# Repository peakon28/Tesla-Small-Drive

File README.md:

# Tesla-Small-Drive

Tesla Model S and X Small Drive unit based on Damien Maguire design using Open Inverter software by Johanes Hubner. Design in Kicad 9
<br>
(

<br>

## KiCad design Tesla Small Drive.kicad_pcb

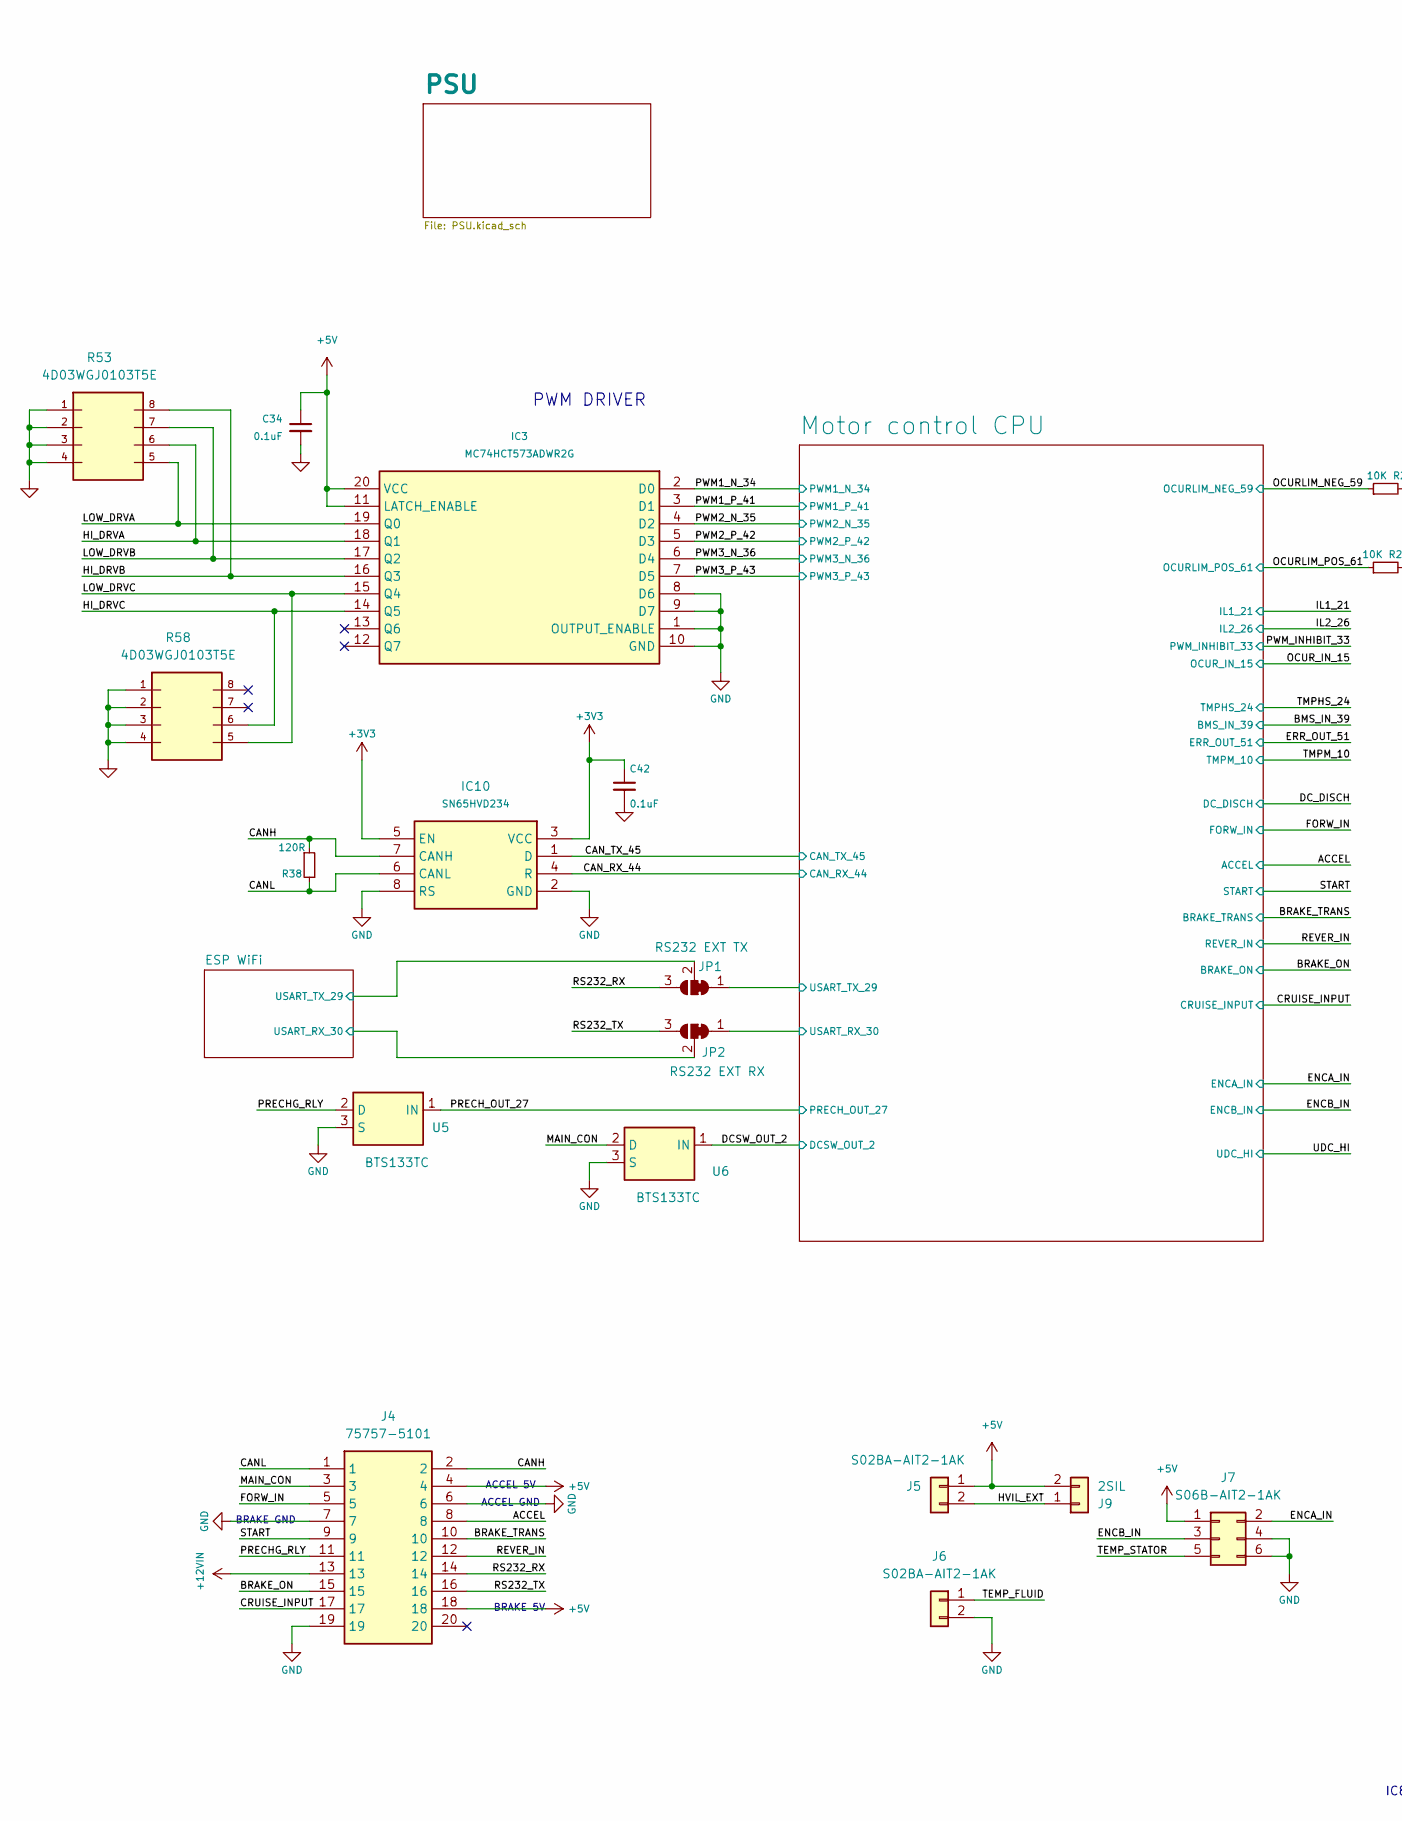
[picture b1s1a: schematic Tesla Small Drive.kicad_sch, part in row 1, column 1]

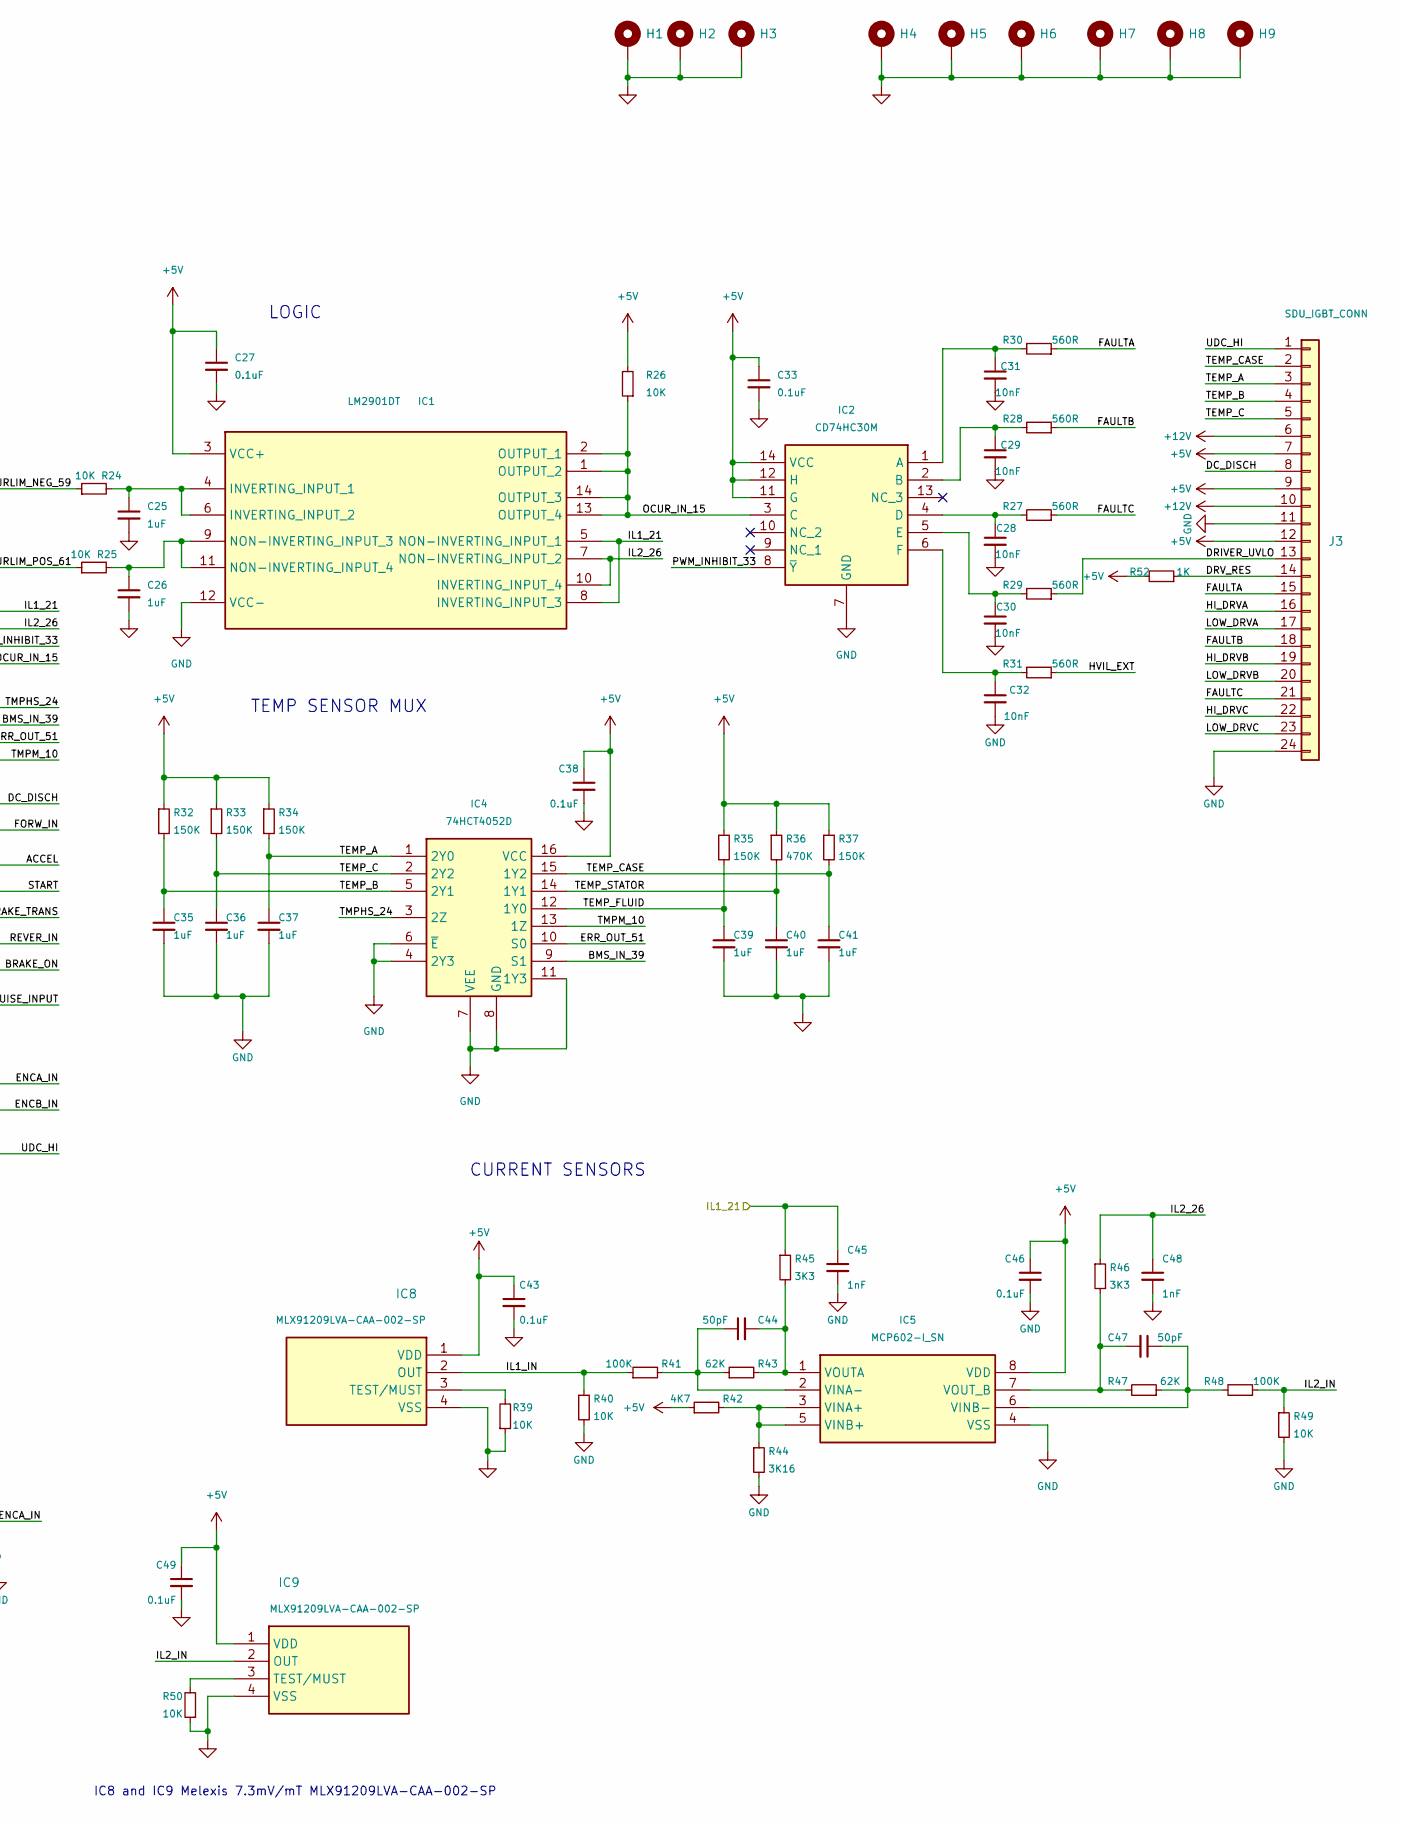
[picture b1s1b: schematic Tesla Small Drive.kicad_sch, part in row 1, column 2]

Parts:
C25, C26, C35, C36, C37, C39, C40, C41: 1uF; C_0603_1608Metric
C27, C33, C34, C38, C42, C43, C46, C49: 0.1uF; C_0603_1608Metric
C28, C29, C30, C31, C32: 10nF; C_0603_1608Metric
C44, C47: 50pF; C_0603_1608Metric
C45, C48: 1nF; C_0603_1608Metric
H1, H2, H3, H4, H5, H6, H7, H8, H9: MountingHole_Pad; MountingHole_4mm_Pad_Via
IC1: LM2901DT; SOIC127P600X175-14N; Manufacturer_Part_Number LM2901DT; Mouser Part Number 511-LM2901DT
IC2: CD74HC30M; SOIC127P600X175-14N; Manufacturer_Part_Number CD74HC30M; Mouser Part Number 595-CD74HC30M
IC3: MC74HCT573ADWR2G; SOIC-20; Manufacturer_Part_Number MC74HCT573ADWR2G; Mouser Part Number 863-MC74HCT573ADWR2G
IC4: 74HCT4052D; SOIC127P600X175-16N; Manufacturer_Part_Number 74HCT4052D; Mouser Part Number 771-74HCT4052D
IC5: MCP602-I_SN; SOIC127P600X175-8N; Manufacturer_Part_Number MCP602-I/SN; Mouser Part Number 579-MCP602ISN
IC8, IC9: MLX91209LVA-CAA-002-SP; MLX91209LVACAA002SP; Manufacturer_Part_Number MLX91209LVA-CAA-002-SP; Mouser Part Number 482-91209LVACAA002SP
IC10: SN65HVD234; SOIC127P599X175-8N; Manufacturer_Part_Number SN65HVD234DR; Mouser Part Number 595-SN65HVD234DR
J3: SDU_IGBT_CONN; RHDR24W76P254_2X12_3048X508X826P
J4: 75757-5101; 75757-5101 footprint; Manufacturer_Part_Number 75757-5101; Mouser Part Number 538-75757-5101
J5, J6: S02BA-AIT2-1AK
J7: S06B-AIT2-1AK
J9: 2SIL; PinHeader_1x02_P2.54mm_Vertical
JP1: RS232 EXT TX; SolderJumper-3_P1.3mm_Bridged12_RoundedPad1.0x1.5mm
JP2: RS232 EXT RX; SolderJumper-3_P1.3mm_Bridged12_RoundedPad1.0x1.5mm
R24, R25, R26, R39, R40, R49, R50: 10K; R_0603_1608Metric
R27, R28, R29, R30, R31: 560R; R_0603_1608Metric
R32, R33, R34, R35, R37: 150K; R_0603_1608Metric
R36: 470K; R_0603_1608Metric
R38: 120R; R_0603_1608Metric
R41, R48: 100K; R_0603_1608Metric
R42: 4K7; R_0603_1608Metric
R43, R47: 62K; R_0603_1608Metric
R44: 3K16; R_0603_1608Metric
R45, R46: 3K3; R_0603_1608Metric
R52: 1K; R_0603_1608Metric
R53, R58: 4D03WGJ0103T5E; RESCAXS80P320X160X60-8N; PARTREV N/A
U5, U6: BTS133TC; TO254P1524X457-3N

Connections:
+3V3: C42.1, IC10.3 (VCC), IC10.5 (EN); also elsewhere on the board
+5V: C27.1, C33.1, C34.1, C38.1, C43.1, C46.1, C49.1, IC1.3 (VCC+), IC2.11 (G), IC2.12 (H), IC2.14 (VCC), IC3.11 (LATCH_ENABLE), IC3.20 (VCC), IC4.16 (VCC), IC5.8 (VDD), IC8.1 (VDD), IC9.1 (VDD), J3.7, J3.9, J3.12, J4.4, J4.18, J5.1, J7.1, J9.2, R26.2, R32.1, R33.1, R34.1, R35.1, R36.1, R37.1, R42.1, R52.2; also elsewhere on the board
+12V: J3.6, J3.10; also elsewhere on the board
+12VIN: J4.13; also elsewhere on the board
/ACCEL: J4.8; also elsewhere on the board
/BMS_IN_39: IC4.9 (S1); also elsewhere on the board
/BRAKE_ON: J4.15; also elsewhere on the board
/BRAKE_TRANS: J4.10; also elsewhere on the board
/CANH: IC10.7 (CANH), J4.2, R38.1
/CANL: IC10.6 (CANL), J4.1, R38.2
/CAN_RX_44: IC10.4 (R); also elsewhere on the board
/CAN_TX_45: IC10.1 (D); also elsewhere on the board
/CRUISE_INPUT: J4.17; also elsewhere on the board
/DCSW_OUT_2: U6.1 (IN); also elsewhere on the board
/DC_DISCH: J3.8; also elsewhere on the board
/DRIVER_UVLO: J3.13, R29.1
/DRV_RES: J3.14, R52.1
/ENCA_IN: J7.2; also elsewhere on the board
/ENCB_IN: J7.3; also elsewhere on the board
/ERR_OUT_51: IC4.10 (S0); also elsewhere on the board
/ESP WiFi/RX: JP1.2 (C); also elsewhere on the board
/ESP WiFi/TX: JP2.2 (C); also elsewhere on the board
/FAULTA: J3.15, R30.1
/FAULTB: J3.18, R28.1
/FAULTC: J3.21, R27.1
/FORW_IN: J4.5; also elsewhere on the board
/HI_DRVA: IC3.18 (Q1), J3.16, R53.6
/HI_DRVB: IC3.16 (Q3), J3.19, R53.8
/HI_DRVC: IC3.14 (Q5), J3.22, R58.6
/HVIL_EXT: J5.2, J9.1, R31.1
/IL1_21: C45.1, IC1.5 (NON-INVERTING_INPUT_1), IC1.8 (INVERTING_INPUT_3), R45.1; also elsewhere on the board
/IL1_IN: IC8.2 (OUT), R40.1, R41.1
/IL2_26: C48.1, IC1.7 (NON-INVERTING_INPUT_2), IC1.10 (INVERTING_INPUT_4), R46.1; also elsewhere on the board
/IL2_IN: IC9.2 (OUT), R48.1, R49.1
/LOW_DRVA: IC3.19 (Q0), J3.17, R53.5
/LOW_DRVB: IC3.17 (Q2), J3.20, R53.7
/LOW_DRVC: IC3.15 (Q4), J3.23, R58.5
/MAIN_CON: J4.3, U6.2 (D)
/Motor control CPU/USART_RX_30: JP2.1 (A); also elsewhere on the board
/Motor control CPU/USART_TX_29: JP1.1 (A); also elsewhere on the board
/OCURLIM_NEG_59: R24.1; also elsewhere on the board
/OCURLIM_POS_61: R25.1; also elsewhere on the board
/OCUR_IN_15: IC1.1 (OUTPUT_2), IC1.2 (OUTPUT_1), IC1.13 (OUTPUT_4), IC1.14 (OUTPUT_3), IC2.3 (C), R26.1; also elsewhere on the board
/PRECHG_RLY: J4.11, U5.2 (D)
/PRECH_OUT_27: U5.1 (IN); also elsewhere on the board
/PWM1_N_34: IC3.2 (D0); also elsewhere on the board
/PWM1_P_41: IC3.3 (D1); also elsewhere on the board
/PWM2_N_35: IC3.4 (D2); also elsewhere on the board
/PWM2_P_42: IC3.5 (D3); also elsewhere on the board
/PWM3_N_36: IC3.6 (D4); also elsewhere on the board
/PWM3_P_43: IC3.7 (D5); also elsewhere on the board
/PWM_INHIBIT_33: IC2.8 (~Y); also elsewhere on the board
/REVER_IN: J4.12; also elsewhere on the board
/RS232_RX: J4.14, JP1.3 (B)
/RS232_TX: J4.16, JP2.3 (B)
/START: J4.9; also elsewhere on the board
/TEMP_A: C37.1, IC4.1 (2Y0), J3.3, R34.2
/TEMP_B: C35.1, IC4.5 (2Y1), J3.4, R32.2
/TEMP_C: C36.1, IC4.2 (2Y2), J3.5, R33.2
/TEMP_CASE: C41.1, IC4.15 (1Y2), J3.2, R37.2
/TEMP_FLUID: C39.1, IC4.12 (1Y0), J6.1, R35.2
/TEMP_STATOR: C40.1, IC4.14 (1Y1), J7.5, R36.2
/TMPHS_24: IC4.3 (2Z); also elsewhere on the board
/TMPM_10: IC4.13 (1Z); also elsewhere on the board
/UDC_HI: J3.1; also elsewhere on the board
GND: C25.2, C26.2, C27.2, C28.2, C29.2, C30.2, C31.2, C32.2, C33.2, C34.2, C35.2, C36.2, C37.2, C38.2, C39.2, C40.2, C41.2, C42.2, C43.2, C45.2, C46.2, C48.2, C49.2, H1.1, H2.1, H3.1, H4.1, H5.1, H6.1, H7.1, H8.1, H9.1, IC1.12 (VCC-), IC2.7 (GND), IC3.1 (OUTPUT_ENABLE), IC3.8 (D6), IC3.9 (D7), IC3.10 (GND), IC4.4 (2Y3), IC4.6 (~E), IC4.7 (VEE), IC4.8 (GND), IC4.11 (1Y3), IC5.4 (VSS), IC8.4 (VSS), IC9.4 (VSS), IC10.2 (GND), IC10.8 (RS), J3.11, J3.24, J4.6, J4.7, J4.19, J6.2, J7.4, J7.6, R39.1, R40.2, R44.2, R49.2, R50.1, R53.1, R53.2, R53.3, R53.4, R58.1, R58.2, R58.3, R58.4, U5.3 (S), U6.3 (S); also elsewhere on the board
unnamed: C25.1, IC1.4 (INVERTING_INPUT_1), IC1.6 (INVERTING_INPUT_2), R24.2
unnamed: C26.1, IC1.9 (NON-INVERTING_INPUT_3), IC1.11 (NON-INVERTING_INPUT_4), R25.2
unnamed: C31.1, IC2.1 (A), R30.2
unnamed: C29.1, IC2.2 (B), R28.2
unnamed: C28.1, IC2.4 (D), R27.2
unnamed: C30.1, IC2.5 (E), R29.2
unnamed: C32.1, IC2.6 (F), R31.2
unnamed: IC5.3 (VINA+), IC5.5 (VINB+), R42.2, R44.1
unnamed: C44.1, IC5.2 (VINA-), R41.2, R43.1
unnamed: C47.1, IC5.6 (VINB-), R47.1, R48.2
unnamed: C44.2, IC5.1 (VOUTA), R43.2, R45.2
unnamed: C47.2, IC5.7 (VOUT_B), R46.2, R47.2
unnamed: IC8.3 (TEST/MUST), R39.2
unnamed: IC9.3 (TEST/MUST), R50.2

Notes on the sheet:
BRAKE 5V
PWM DRIVER
IC8 and IC9 Melexis 7.3mV/mT MLX91209LVA-CAA-002-SP
TEMP SENSOR MUX
LOGIC
BRAKE GND
ACCEL GND
ACCEL 5V
CURRENT SENSORS

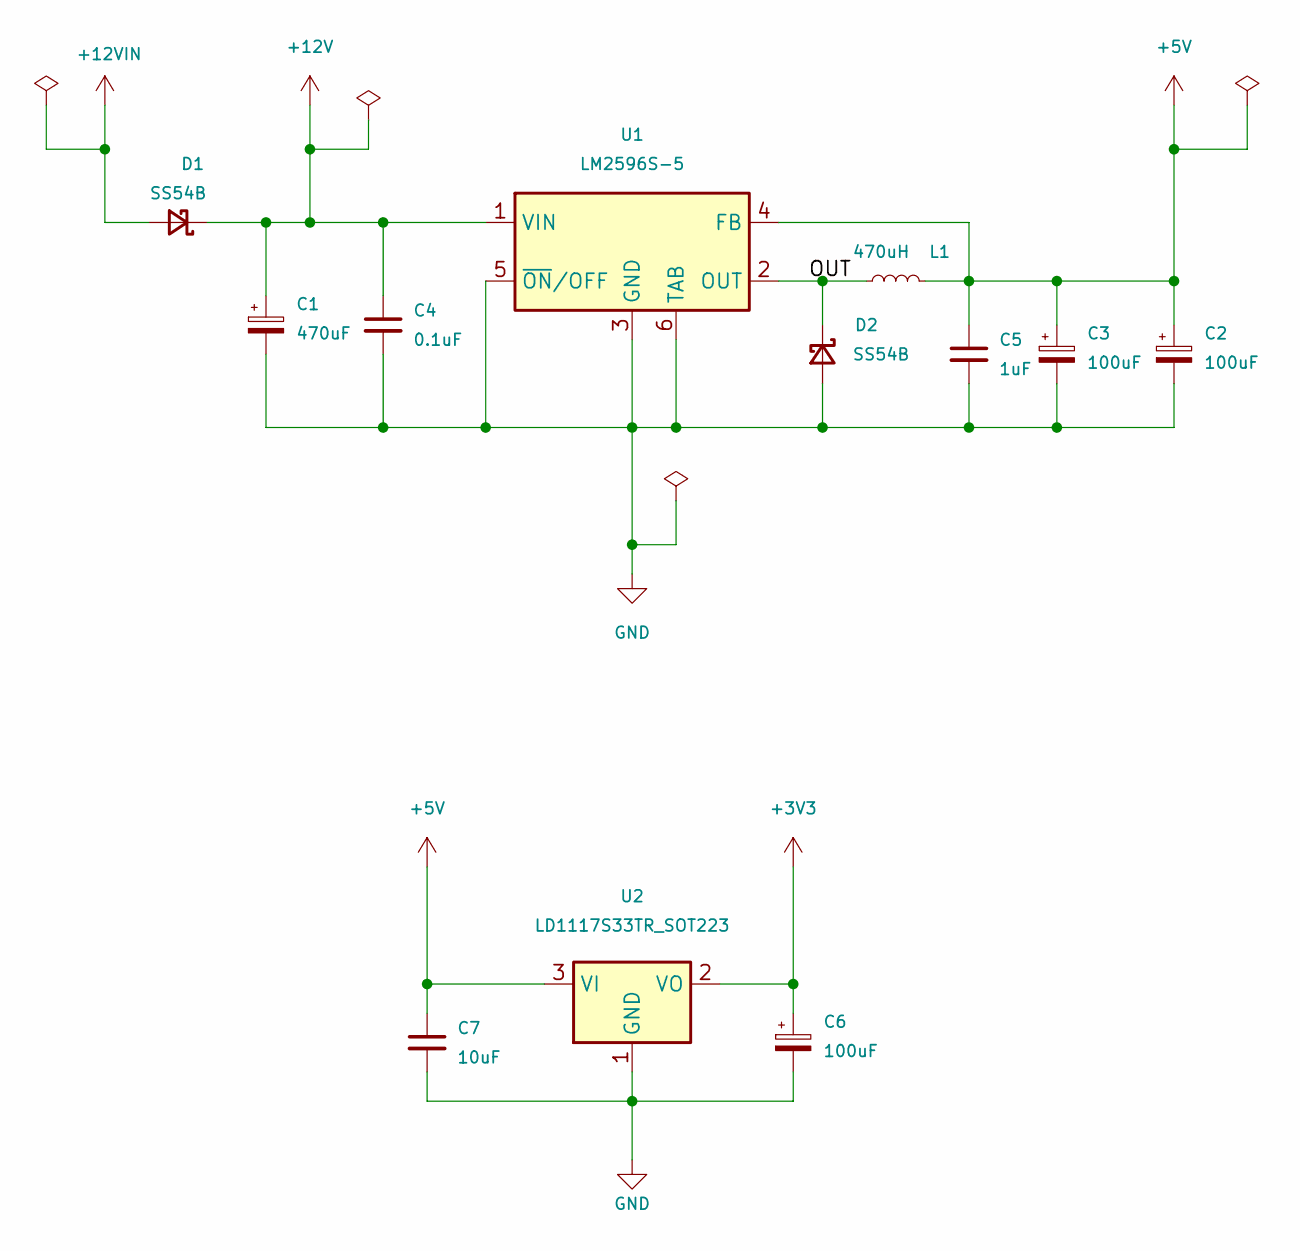
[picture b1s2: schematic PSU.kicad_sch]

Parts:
C1: 470uF; CP_Elec_10x10; JLCPCB Part # C3351
C2, C3, C6: 100uF; CP_EIA-3528-21_Kemet-B; JLCPCB Part # C16133
C4: 0.1uF; C_0603_1608Metric
C5: 1uF; C_0603_1608Metric
C7: 10uF; C_0603_1608Metric
D1, D2: SS54B; DIOM4336X244N; JLCPCB Part # C698840
L1: 470uH; L_Sunlord_SWRB1207S; JLCPCB Part # C169382
U1: LM2596S-5; TO-263-5_TabPin6; LCSC Part # C10002
U2: LD1117S33TR_SOT223; SOT-223-3_TabPin2; JLCPCB Part # C347229

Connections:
+3V3: C6.1, U2.2 (VO); also elsewhere on the board
+5V: C2.1, C3.1, C5.1, C7.1, L1.2, U1.4 (FB), U2.3 (VI); also elsewhere on the board
+12V: C1.1, C4.1, D1.C (K), U1.1 (VIN); also elsewhere on the board
+12VIN: D1.A; also elsewhere on the board
/PSU/OUT: D2.C (K), L1.1, U1.2 (OUT)
GND: C1.2, C2.2, C3.2, C4.2, C5.2, C6.2, C7.2, D2.A, U1.3 (GND), U1.5 (~ON/OFF), U1.6 (TAB), U2.1 (GND); also elsewhere on the board

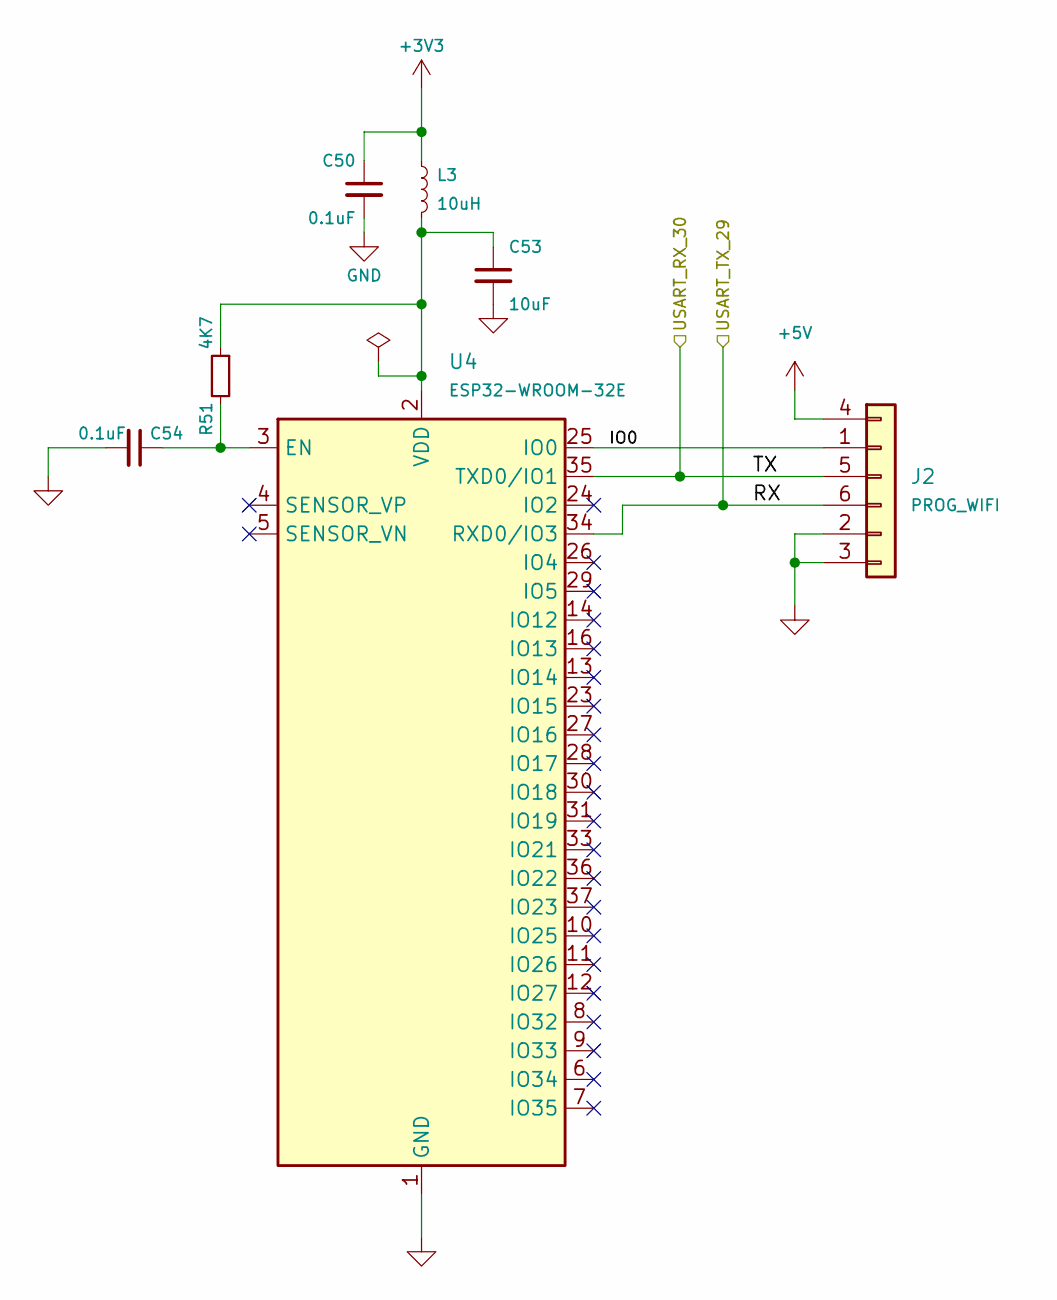
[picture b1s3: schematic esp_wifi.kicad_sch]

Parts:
C50, C54: 0.1uF; C_0603_1608Metric
C53: 10uF; C_0603_1608Metric
J2: PROG_WIFI; PinHeader_1x06_P2.54mm_Vertical
L3: 10uH; L_0603_1608Metric
R51: 4K7; R_0603_1608Metric
U4: ESP32-WROOM-32E; ESP32-WROOM-32D

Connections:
+3V3: C50.1, L3.1; also elsewhere on the board
+5V: J2.4; also elsewhere on the board
/ESP WiFi/IO0: J2.1, U4.25 (IO0)
/ESP WiFi/RX: J2.6, U4.34 (RXD0/IO3); also elsewhere on the board
/ESP WiFi/TX: J2.5, U4.35 (TXD0/IO1); also elsewhere on the board
GND: C50.2, C53.2, C54.2, J2.2, J2.3, U4.1 (GND), U4.15 (GND), U4.38 (GND), U4.39 (GND); also elsewhere on the board
unnamed: C54.1, R51.2, U4.3 (EN)
unnamed: C53.1, L3.2, R51.1, U4.2 (VDD)

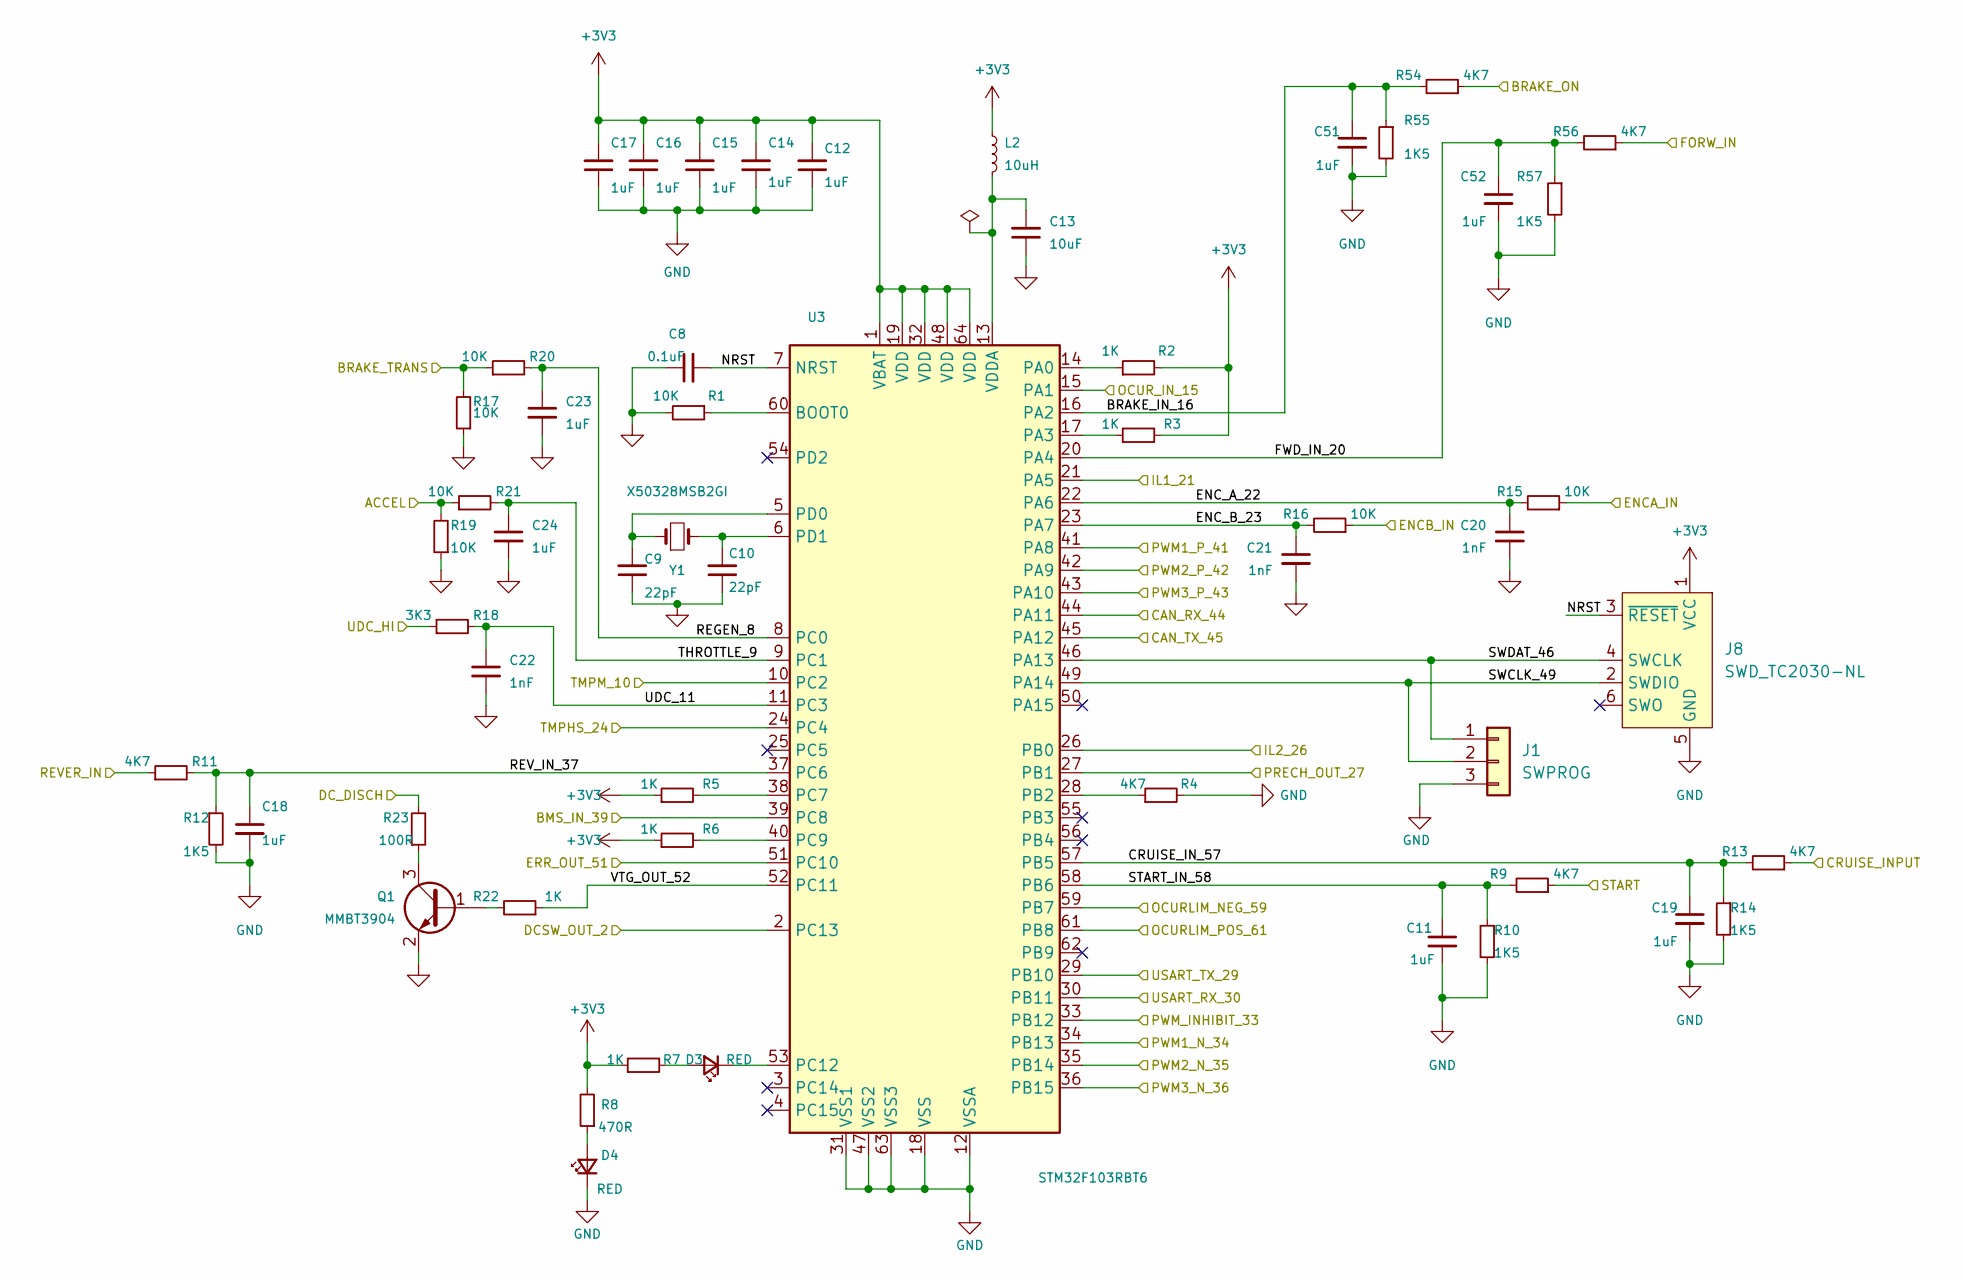
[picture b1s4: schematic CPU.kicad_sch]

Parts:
C8: 0.1uF; C_0603_1608Metric
C9, C10: 22pF; C_0603_1608Metric
C11, C12, C14, C15, C16, C17, C18, C19, C23, C24, C51, C52: 1uF; C_0603_1608Metric
C13: 10uF; C_0603_1608Metric
C20, C21, C22: 1nF; C_0603_1608Metric
D3, D4: RED; LED_0603_1608Metric
J1: SWPROG; PinHeader_1x03_P2.54mm_Vertical
J8: SWD_TC2030-NL; Tag-Connect_TC2030-IDC-NL_2x03_P1.27mm_Vertical
L2: 10uH; L_0603_1608Metric
Q1: MMBT3904; SOT-23
R1, R15, R16, R17, R19, R20, R21: 10K; R_0603_1608Metric
R2, R3, R5, R6, R7, R22: 1K; R_0603_1608Metric
R4, R9, R11, R13, R54, R56: 4K7; R_0603_1608Metric
R8: 470R; R_0603_1608Metric
R10, R12, R14, R55, R57: 1K5; R_0603_1608Metric
R18: 3K3; R_0603_1608Metric
R23: 100R; R_0603_1608Metric
U3: STM32F103RBT6; LQFP-64_10x10mm_P0.5mm
Y1: X50328MSB2GI; RESC5032X135N

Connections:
+3V3: C12.2, C14.2, C15.2, C16.2, C17.2, J8.1 (VCC), L2.1, R2.2, R3.2, R5.1, R6.1, R7.1, R8.2, U3.1 (VBAT), U3.19 (VDD), U3.32 (VDD), U3.48 (VDD), U3.64 (VDD); also elsewhere on the board
/ACCEL: R19.2, R21.1; also elsewhere on the board
/BMS_IN_39: U3.39 (PC8); also elsewhere on the board
/BRAKE_ON: R54.1; also elsewhere on the board
/BRAKE_TRANS: R17.2, R20.1; also elsewhere on the board
/CAN_RX_44: U3.44 (PA11); also elsewhere on the board
/CAN_TX_45: U3.45 (PA12); also elsewhere on the board
/CRUISE_INPUT: R13.1; also elsewhere on the board
/DCSW_OUT_2: U3.2 (PC13); also elsewhere on the board
/DC_DISCH: R23.2; also elsewhere on the board
/ENCA_IN: R15.1; also elsewhere on the board
/ENCB_IN: R16.1; also elsewhere on the board
/ERR_OUT_51: U3.51 (PC10); also elsewhere on the board
/FORW_IN: R56.1; also elsewhere on the board
/IL1_21: U3.21 (PA5); also elsewhere on the board
/IL2_26: U3.26 (PB0); also elsewhere on the board
/Motor control CPU/BRAKE_IN_16: C51.1, R54.2, R55.1, U3.16 (PA2)
/Motor control CPU/CRUISE_IN_57: C19.1, R13.2, R14.1, U3.57 (PB5)
/Motor control CPU/ENC_A_22: C20.1, R15.2, U3.22 (PA6)
/Motor control CPU/ENC_B_23: C21.1, R16.2, U3.23 (PA7)
/Motor control CPU/FWD_IN_20: C52.1, R56.2, R57.1, U3.20 (PA4)
/Motor control CPU/NRST: C8.2, J8.3 (~RESET), U3.7 (NRST)
/Motor control CPU/REGEN_8: C23.1, R20.2, U3.8 (PC0)
/Motor control CPU/REV_IN_37: C18.1, R11.2, R12.1, U3.37 (PC6)
/Motor control CPU/START_IN_58: C11.1, R9.2, R10.1, U3.58 (PB6)
/Motor control CPU/SWCLK_49: J1.2, J8.2 (SWDIO), U3.49 (PA14)
/Motor control CPU/SWDAT_46: J1.1, J8.4 (SWCLK), U3.46 (PA13)
/Motor control CPU/THROTTLE_9: C24.1, R21.2, U3.9 (PC1)
/Motor control CPU/UDC_11: C22.1, R18.2, U3.11 (PC3)
/Motor control CPU/USART_RX_30: U3.30 (PB11); also elsewhere on the board
/Motor control CPU/USART_TX_29: U3.29 (PB10); also elsewhere on the board
/Motor control CPU/VTG_OUT_52: R22.1, U3.52 (PC11)
/OCURLIM_NEG_59: U3.59 (PB7); also elsewhere on the board
/OCURLIM_POS_61: U3.61 (PB8); also elsewhere on the board
/OCUR_IN_15: U3.15 (PA1); also elsewhere on the board
/PRECH_OUT_27: U3.27 (PB1); also elsewhere on the board
/PWM1_N_34: U3.34 (PB13); also elsewhere on the board
/PWM1_P_41: U3.41 (PA8); also elsewhere on the board
/PWM2_N_35: U3.35 (PB14); also elsewhere on the board
/PWM2_P_42: U3.42 (PA9); also elsewhere on the board
/PWM3_N_36: U3.36 (PB15); also elsewhere on the board
/PWM3_P_43: U3.43 (PA10); also elsewhere on the board
/PWM_INHIBIT_33: U3.33 (PB12); also elsewhere on the board
/REVER_IN: R11.1; also elsewhere on the board
/START: R9.1; also elsewhere on the board
/TMPHS_24: U3.24 (PC4); also elsewhere on the board
/TMPM_10: U3.10 (PC2); also elsewhere on the board
/UDC_HI: R18.1; also elsewhere on the board
GND: C8.1, C9.1, C10.1, C11.2, C12.1, C13.1, C14.1, C15.1, C16.1, C17.1, C18.2, C19.2, C20.2, C21.2, C22.2, C23.2, C24.2, C51.2, C52.2, D4.1 (K), J1.3, J8.5 (GND), Q1.2 (E), R1.2, R4.2, R10.2, R12.2, R14.2, R17.1, R19.1, R55.2, R57.2, U3.12 (VSSA), U3.18 (VSS), U3.31 (VSS), U3.47 (VSS2), U3.63 (VSS3); also elsewhere on the board
unnamed: D3.2 (A), R7.2
unnamed: D3.1 (K), U3.53 (PC12)
unnamed: D4.2 (A), R8.1
unnamed: Q1.1 (B), R22.2
unnamed: Q1.3 (C), R23.1
unnamed: R1.1, U3.60 (BOOT0)
unnamed: R2.1, U3.14 (PA0)
unnamed: R3.1, U3.17 (PA3)
unnamed: R4.1, U3.28 (PB2)
unnamed: R5.2, U3.38 (PC7)
unnamed: R6.2, U3.40 (PC9)
unnamed: C9.2, U3.5 (PD0), Y1.1
unnamed: C10.2, U3.6 (PD1), Y1.2
unnamed: C13.2, L2.2, U3.13 (VDDA)

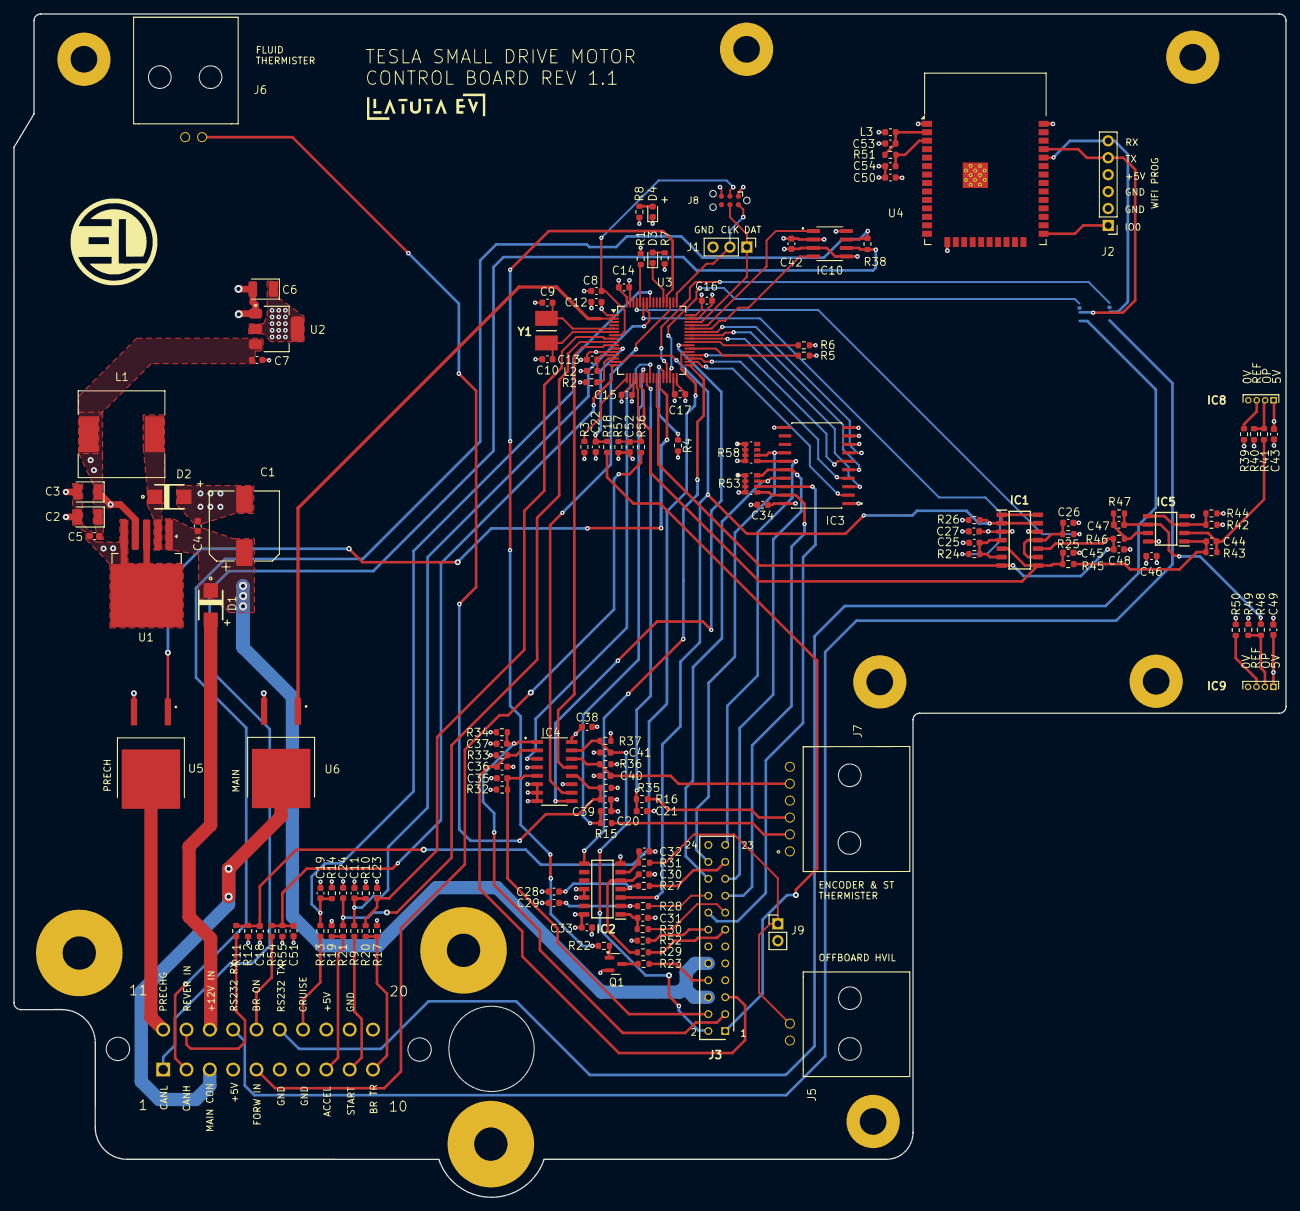
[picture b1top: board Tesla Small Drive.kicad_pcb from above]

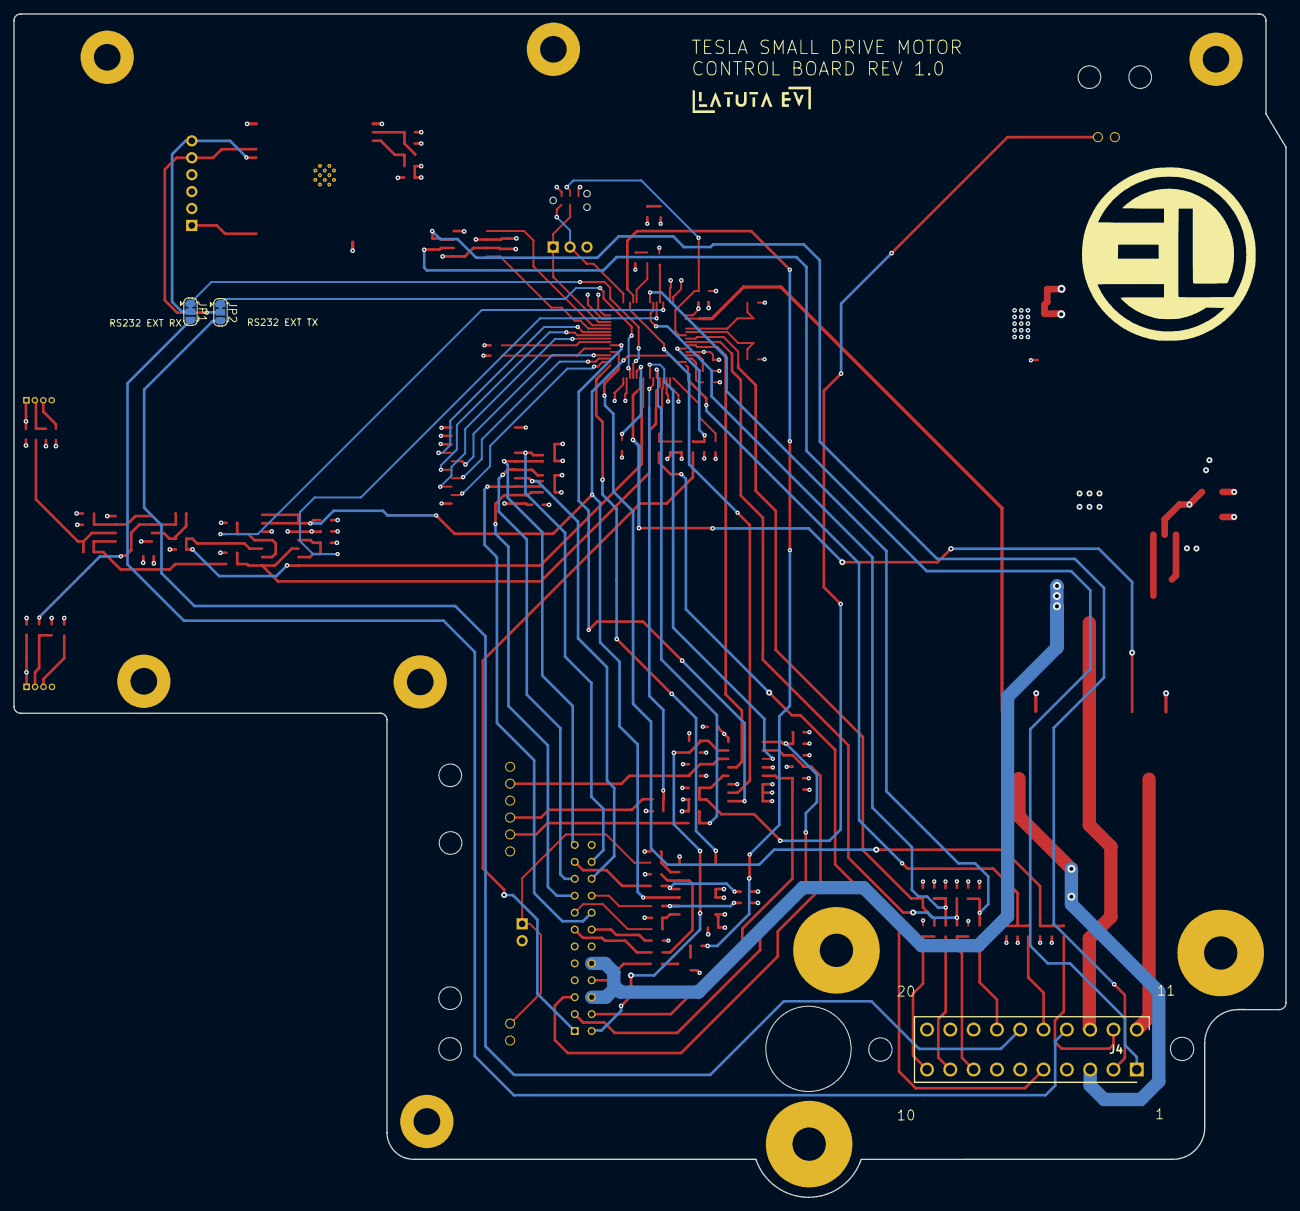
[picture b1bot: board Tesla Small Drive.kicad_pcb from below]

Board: 4 copper layers, 191.0 x 177.7 mm, 155 parts (3 on the bottom side), 112 nets.

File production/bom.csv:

Designator,Footprint,Quantity,Value,LCSC Part #
C1,CP_Elec_10x10,1,470uF, C3351
"C10, C9",0603,2,22pF,
"C11, C12, C14, C15, C16, C17, C18, C19, C23, C24, C25, C26, C35, C36, C37, C39, C40, C41, C5, C51, C52",0603,21,1uF,
"C13, C53, C7",0603,3,10uF,
"C2, C3, C6",CP_EIA-3528-21_Kemet-B,3,100uF,C16133
"C20, C21, C22, C45, C48",0603,5,1nF,
"C27, C33, C34, C38, C4, C42, C43, C46, C49, C50, C54, C8",0603,12,0.1uF,
"C28, C29, C30, C31, C32",0603,5,10nF,
"C44, C47",0603,2,50pF,
"D1, D2",DIOM4336X244N,2,SS54B,C698840
"D3, D4",0603,2,RED,
IC1,SOIC127P600X175-14N,1,LM2901DT,C142961
IC10,SOIC127P599X175-8N,1,SN65HVD234,
IC2,SOIC127P600X175-14N,1,CD74HC30M, C6540
IC3,SOIC-20,1,MC74HCT573ADWR2G, C233618
IC4,SOIC127P600X175-16N,1,74HCT4052D,C87281
IC5,SOIC127P600X175-8N,1,MCP602-I_SN,C29605
J2,PinHeader_1x06_P2.54mm_Vertical,1,PROG_WIFI,
L1,L_Sunlord_SWRB1207S,1,470uH,C169382 
"L2, L3",0603,2,10uH,
Q1,SOT-23,1,MMBT3904,
"R1, R15, R16, R17, R19, R20, R21, R24, R25, R26, R39, R40, R49, R50",0603,14,10K,
"R10, R12, R14, R55, R57",0603,5,1K5,
"R11, R13, R4, R42, R51, R54, R56, R9",0603,8,4K7,
"R18, R45, R46",0603,3,3K3,
"R2, R22, R3, R5, R52, R6, R7",0603,7,1K,
R23,0603,1,100R,
"R27, R28, R29, R30, R31",0603,5,560R,
"R32, R33, R34, R35, R37",0603,5,150K,
R36,0603,1,470K,
R38,0603,1,120R,
"R41, R48",0603,2,100K,
"R43, R47",0603,2,62K,
R44,0603,1,3K16,
"R53, R58",RESCAXS80P320X160X60-8N,2,4D03WGJ0103T5E,
R8,0603,1,470R,
U1,TO-263-5_TabPin6,1,LM2596S-5, C10002
U2,SOT-223-3_TabPin2,1,LD1117S33TR_SOT223,C347229
U3,LQFP-64_10x10mm_P0.5mm,1,STM32F103RBT6,
U4,ESP32-WROOM-32D,1,ESP32-WROOM-32E,
"U5, U6",TO254P1524X457-3N,2,BTS133TC,
Y1,RESC5032X135N,1,X50328MSB2GI,

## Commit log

2025-08-25 25-08-25 first release
    Tesla Small drive board my version in Kicad based on Damien Maguire design
